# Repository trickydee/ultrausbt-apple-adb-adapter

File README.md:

# Apple ADB USB & Bluetooth Adapter

**Firmware v2.2.3** · Product: **ultrausbt-Apple-ADB-adapter** · License: [GPL-3.0-or-later](./LICENSE) · [COPYING](./COPYING) · [Release notes](./docs/release-notes.md)

## Overview

This project uses a Raspberry Pi Pico to connect modern USB and Bluetooth devices such as keyboards, mice, trackballs, and gamepads to classic Apple Desktop Bus (ADB) computers.

It targets **68K Macintosh** (Classic / LC / Quadra-class), **early PowerPC** ADB Macs (Performa / Power Macintosh), and the **Apple IIgs**.
It should also work with ADB-enabled **NeXT** machines, but these have **not** been tested yet.

A design for a reference adapter is included in the repo. The adapter is bi-directional and can be toggled between device or host mode:

* **ADB Device** mode (default): attach USB and Bluetooth devices to an ADB host computer.

* **ADB Host** mode: connect original ADB devices (keyboard, mouse, trackballs, …) to a USB HID host such as a modern PC or Mac

The hardware can be configured with dual Mini-DIN ADB ports, wired as a bus **pass-through**: you can daisy-chain real ADB keyboards, mice, trackballs, and other devices alongside the adapter’s USB/BT emulation (see [`docs/adb-passthrough-hub.md`](./docs/adb-passthrough-hub.md)).

If you are using a **Pico 2 W** you can mix USB and Bluetooth devices. USB-only builds work on Pico / Pico 2 as well. A **Pico 2 W** is recommended for the full feature set (Bluetooth + Device/Host toggle).

**This project and firmware descend from the HIDHopper ADB project and its upstream line (including QuokkADB / adbuino)** (GPL) — see Acknowledgements below.

## USB device support

* USB HID keyboards
* USB HID mice (and many trackballs that appear as mice)
* Bluetooth keyboards, mice, and one gamepad slot on Pico W / Pico 2 W (see Bluetooth support)

## Game controller support (Bluetooth)

One Bluetooth gamepad can be connected (Bluepad32). **Phase B** maps D-pad/buttons to keyboard keys and the left stick to mouse movement — useful without native ADB joystick firmware. Details: [`docs/gamepad-support.md`](./docs/gamepad-support.md).

Native Gravis MouseStick II (handler **0x23**) is planned for the future; see [`docs/FUTURE_WORK.md`](./docs/FUTURE_WORK.md).

# Usage

## USB

Connect devices to the Pico USB port (use a powered USB OTG hub if you need several). Supported keyboards and mice should enumerate within a few seconds; confirm on the OLED.

**Before powering on the Mac:** plug the adapter into ADB (and any pass-through ADB devices into the second port), attach USB/BT peripherals, then power on the host. **You should not hot-plug** ADB devices while the vintage machine is running.

## Bluetooth support (Pico W / Pico 2 W)

Bluetooth keyboards, mice, and gamepads are supported via [Bluepad32](https://github.com/ricardoquesada/bluepad32). You can run a mostly wireless ADB setup, or mix USB and Bluetooth. Prefer **Pico 2 W** for Bluetooth builds.

### Pairing

1. Put the Bluetooth device into pairing mode.
2. Confirm it on the OLED **Devices** / **Map Devices** screens.
3. Recommended order when pairing several devices (especially on Mac cold boot): **mouse → keyboard → gamepad**.

To clear stored pairing keys, hold **˄ + ˯** (Up + Down) for about five seconds (Map Devices shows `^+~ Clear Pair`).

More detail: [`docs/bluetooth-pairing.md`](./docs/bluetooth-pairing.md).

## ADB Device mode (USB/BT → vintage ADB host)

Default mode. Attach USB and Bluetooth keyboards, mice, trackballs, and (on Pico W / Pico 2 W) a gamepad to an ADB host:

* Apple IIgs
* Macintosh 68K (Classic / LC / Quadra-class)
* Early PowerPC ADB Macs

**NeXT** machines have **not** been tested yet.

Pass-through port: real ADB devices can share the bus with the adapter.

## ADB Host mode (ADB devices → modern USB host)

Connect ADB devices (keyboard, mouse, trackball, …) to a USB host such as a modern PC or Mac. The adapter polls the ADB bus and presents them as USB HID.

* Switch with **`*`** from any OLED screen, or use the **ADB Mode** page (`#` carousel → Mode; `˄`/`˯` select **ADB Host** / **ADB Device**, `#` apply). Homescreen shows **ADB Host** or **ADB Dev**.
* Vintage Mac / IIgs should be **off and disconnected**; remove USB-A peripherals while in ADB Host mode (Bluetooth is not bridged to the PC in this mode).
* Details: [`docs/adb-host-mode.md`](./docs/adb-host-mode.md).

# OLED UI

An SSD1306 OLED and four buttons are supported on the UltraUSBT ADB board — the display is optional on a bare Pico, but recommended:

| Key | Role |
|-------|------|
| **˄** (Up) | Mode screen: select **ADB Host**; with ˯: clear BT pairings |
| **˯** (Down) | Mode screen: select **ADB Device**; with ˄: clear BT pairings |
| **#** (Center) | Advance screen carousel; Mode screen: apply |
| **\*** | Toggle ADB Device ↔ ADB Host from any screen |

Carousel (host builds): Splash → Devices → Map Devices → ADB Bus → ADB Mode → Splash.

# Hardware

The [`kicad/`](./kicad/) directory holds the **reference board** design for this project (KiCad schematic / PCB — dual Mini-DIN ADB pass-through, BSS138 level shifting, Pico).

Firmware GPIO and power notes: [`docs/hardware.md`](./docs/hardware.md).

# Building the firmware

Download a pre-built UF2 from [Releases](https://github.com/trickydee/ultrausbt-apple-adb-adapter/releases), or build with `./build-all.sh`:

```bash
# Default: Pico 2 W (device + host toggle) → dist/
./build-all.sh

# Quick single-board dev build
./build.sh
```

Flash the matching `.uf2` from `dist/` (hold **BOOTSEL**, copy to the RPI-RP2 drive).

Typical outputs:

* `dist/ultrausbt-Apple-ADB-adapter-firmware-pico2_w-host.uf2` — release image (**ADB Device** and **ADB Host**)
* `dist/ultrausbt-Apple-ADB-adapter-firmware-pico2_w-host-debug.uf2` — UART debug @ 115200 on GP0

If `PICO_SDK_PATH` is unset, the scripts clone the Pico SDK once under `.pico-sdk/`. Optional upstream TinyUSB: `git submodule update --init --recursive`.

# Documentation

| Doc | Topic |
|-----|--------|
| [`docs/release-notes.md`](./docs/release-notes.md) | Firmware changelog |
| [`docs/troubleshooting.md`](./docs/troubleshooting.md) | Common issues, BT pairing, host timing |
| [`docs/bluetooth-pairing.md`](./docs/bluetooth-pairing.md) | Multi-device Bluetooth tips |
| [`docs/adb-host-mode.md`](./docs/adb-host-mode.md) | ADB Host mode (ADB devices → modern USB host) |
| [`docs/adb-passthrough-hub.md`](./docs/adb-passthrough-hub.md) | Pass-through / hub behaviour |
| [`docs/gamepad-support.md`](./docs/gamepad-support.md) | BT gamepad mapping |
| [`docs/iigs-debugging.md`](./docs/iigs-debugging.md) | IIgs timing notes |
| [`docs/hardware.md`](./docs/hardware.md) | Board / GPIO |
| [`docs/build-flags.md`](./docs/build-flags.md) | CMake options |
| [`docs/FUTURE_WORK.md`](./docs/FUTURE_WORK.md) | Roadmap |
| [`docs/changes.md`](./docs/changes.md) | Version / SDK build notes |
| [`docs/archive/`](./docs/archive/) | Historical port / design notes |
| [`docs/fixtures/`](./docs/fixtures/) | ADB captures (adbmon, Wacom, SE/30) |

## Contributions

This project is open source — pull requests and issues are welcome. See [`CONTRIBUTING.md`](./CONTRIBUTING.md).

# Acknowledgements

This project was made possible by the "HID Hopper" project from Androda which in turn benefited from other upstream projects.

**Upstream — please support the original projects with a GitHub star:**

* **HIDHopper ADB** [HIDHopper_ADB](https://github.com/TechByAndroda/HIDHopper_ADB) — the ADB-on-Pico lineage this firmware continues
* **adbuino** [akuker/adbuino](https://github.com/akuker/adbuino)
* **QuokkADB** [QuokkADB-firmware](https://github.com/rabbitholecomputing/QuokkADB-firmware)
* **tmk_keyboard** [tmk_keyboard](https://github.com/tmk/tmk_keyboard) — ADB protocol foundations
* **bbraun** [bbraun’s adbduino](http://synack.net/svn/adbduino/)
* **Difegue** [Difegue’s updates](https://tvc-16.science/adbuino-ps2.html) — early adbuino / PS/2 work

This fork also relies on:

* [Raspberry Pi Pico SDK](https://github.com/raspberrypi/pico-sdk) — RP2040 / RP2350 platform
* [TinyUSB](https://github.com/hathach/tinyusb) by Ha Thach — USB host and device stacks
* [Bluepad32](https://github.com/ricardoquesada/bluepad32) by Ricardo Quesada — Bluetooth HID

**Other UltraUSBT projects**

If this project is useful you may also want to check out:

* Amiga Keyboard and Dual DSub 9 pin adapter — [Amiga USB/BT adapter](https://github.com/trickydee/ultrausbt-amiga)

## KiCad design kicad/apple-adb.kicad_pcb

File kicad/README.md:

# UltraUSBT reference hardware

KiCad schematic and PCB files for the UltraUSBT DIY Apple ADB adapter live in this directory.

Firmware GPIO and wiring notes: [`../docs/hardware.md`](../docs/hardware.md).

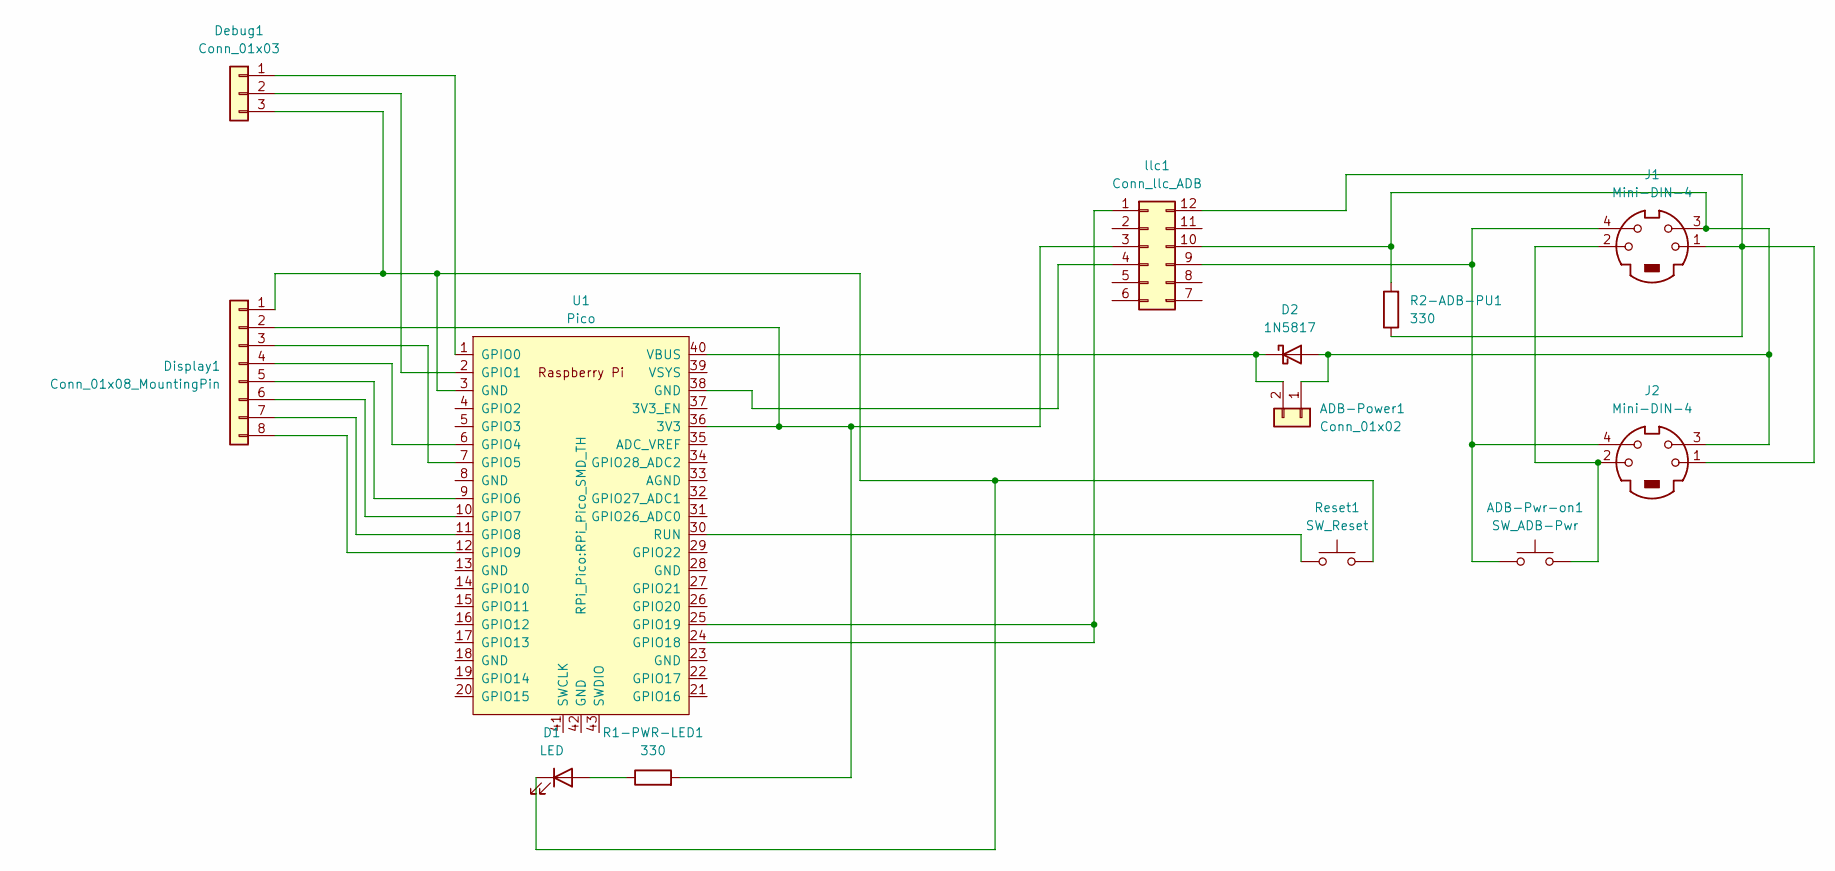
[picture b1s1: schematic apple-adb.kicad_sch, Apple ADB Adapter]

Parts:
ADB-Power1: Conn_01x02; PinSocket_1x02_P2.54mm_Vertical
ADB-Pwr-on1: SW_ADB-Pwr; SW_PUSH_6mm
D1: LED; LED_D3.0mm
D2: 1N5817; D_DO-41_SOD81_P10.16mm_Horizontal
Debug1: Conn_01x03; PinSocket_1x03_P2.54mm_Vertical
Display1: Conn_01x08_MountingPin; PinSocket_1x08_P2.54mm_Vertical
J1, J2: Mini-DIN-4; ADB_MDR4_MINI-DIN
R1-PWR-LED1, R2-ADB-PU1: 330; R_Axial_DIN0204_L3.6mm_D1.6mm_P7.62mm_Horizontal
Reset1: SW_Reset; SW_PUSH_6mm
U1: Pico; RPi_Pico_SMD_TH
llc1: Conn_llc_ADB; DIP-12_W10.16mm

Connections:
unnamed: ADB-Power1.1, D2.2 (A), J1.3, J2.3, R2-ADB-PU1.2, llc1.10 (Pin_b3)
unnamed: ADB-Power1.2, D2.1 (K), U1.40 (VBUS)
unnamed: ADB-Pwr-on1.2, J1.2, J2.2
unnamed 3: D1.2 (A), R1-PWR-LED1.1; also elsewhere on the board
unnamed 4: D1.1 (K), Debug1.3, Display1.1, Reset1.2, U1.3 (GND); also elsewhere on the board
unnamed: Debug1.1, U1.1 (GPIO0)
unnamed: Debug1.2, U1.2 (GPIO1)
unnamed: Display1.2, R1-PWR-LED1.2, U1.36 (3V3), llc1.3 (Pin_a3)
unnamed: Display1.3, U1.7 (GPIO5)
unnamed: Display1.4, U1.6 (GPIO4)
unnamed: Display1.5, U1.9 (GPIO6)
unnamed: Display1.6, U1.10 (GPIO7)
unnamed: Display1.7, U1.11 (GPIO8)
unnamed: Display1.8, U1.12 (GPIO9)
unnamed: U1.24 (GPIO18), U1.25 (GPIO19), llc1.1 (Pin_a1)
unnamed: Reset1.1, U1.30 (RUN)
unnamed: U1.38 (GND), llc1.4 (Pin_a4)
unnamed: J1.1, J2.1, R2-ADB-PU1.1, llc1.12 (Pin_b1)
unnamed: ADB-Pwr-on1.1, J1.4, J2.4, llc1.9 (Pin_b4)

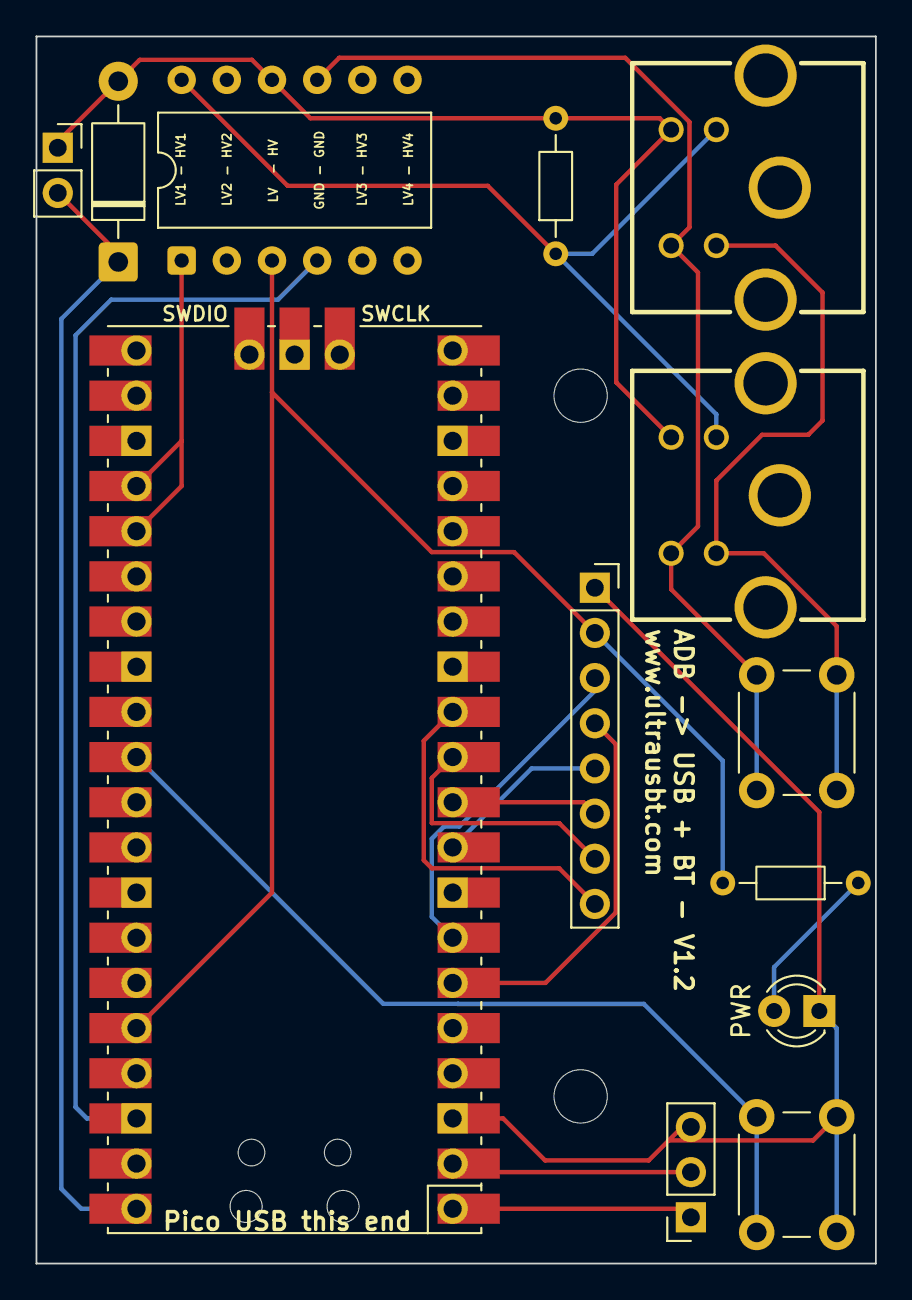
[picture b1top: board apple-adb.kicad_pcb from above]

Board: 2 copper layers, 47.2 x 69.0 mm, 13 parts (0 on the bottom side), 19 nets.

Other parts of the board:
PWR: LED; LED_D3.0mm

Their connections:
unnamed 3: PWR.2 (A); also elsewhere on the board
unnamed 4: PWR.1 (K); also elsewhere on the board

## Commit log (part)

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2026-03-05 Add build setup, update ADB GPIOs, add docs/changes
    - Add top-level Makefile and build.sh for firmware build
    - Update README with build-from-root instructions
    - ADB GPIOs: ADB_OUT_GPIO=18, ADB_IN_GPIO=19 (was 19/20)
    - Fix set_sys_clock_khz: add hardware/clocks.h and hardware_clocks link
    - Add docs/changes.md documenting GPIO configuration
2026-03-05 Add upstream TinyUSB, Blue-QuokkADB name, SDK 2.2.0
    - Add TinyUSB as submodule at src/firmware/tinyusb (optional upstream)
    - Set PICO_TINYUSB_PATH in CMake when tinyusb/hw/bsp/rp2040 present
    - build.sh: init submodules; README and docs/changes: document upstream TinyUSB
    - pico_sdk_import: default fetch tag 2.2.0, GIT_SUBMODULES_RECURSE TRUE
    - Product name: Blue-QuokkADB (platform_config.h)
    - Add <cstdio> in platformkbdparser.cpp and quokkadb.cpp for printf
2026-03-05 Add Bluepad32 (BT keyboard/mouse) and build_all.sh
    - Add bluepad32 submodule, init/platform (keyboard+mouse only), bt_hid_bridge
    - Enable Bluepad32 for pico_w and pico2_w in CMake; feed BT into same ADB parsers as USB
    - Add build_all.sh: build-pico, build-pico_w, build-pico2, build-pico2_w
    - Ignore build-* directories in .gitignore; update docs/changes.md
2026-03-06 Add firmware version (1.0.1), fix flash sector conflict with BTstack
    - Single source of truth: project VERSION in firmware CMakeLists.txt
    - platform_config.h uses HIDHopper ADB version for banner/identity
    - docs/changes.md: document version and how to bump
    - flashsettings: move settings off last sector to avoid BTstack TLV overlap
2026-03-06 CMakeLists.txt: minor whitespace/formatting
2026-03-06 v1.0.2: fix right-mouse hang, add release notes
    - Remove blocking waits in ctrl-click path (usbmouseparser.cpp) so device
    no longer hangs on right mouse button; ctrl-click still works for System 6/7
    - Bump firmware version to 1.0.2
    - Add docs/release-notes.md with 1.0.2 and 1.0.1 entries
2026-03-06 docs: add 1.0.0 release notes (supported boards, Bluepad32)
2026-03-06 Initial screen commit: SSD1306 OLED display (Apple ADB)
    - Add ssd1306 driver and font (from amigahid-pico, MIT)
    - Display module: splash (Apple ADB, version, mode), devices, BT names
    - I2C on GPIO 4/5 (i2c0), buttons 6/7/8; no GPIO collision with ADB/LED/UART
    - Integrate display_init, display_show_splash, display_handle_buttons in main loop
    - BT device counts and display_set_bt_counts when Bluepad32 enabled
    - docs/changes.md: document display GPIOs and config
2026-03-06 Display ADB status (K/M/G, SRQ, collision), fix disconnect detection, build script
    - Splash ADB line: show device IDs (K# M# G#), S for SRQ, ! for collision
    - Only redraw splash on connection/ID change (not SRQ/collision) to avoid
    mouse lag from full-screen I2C refresh
    - Show 'ADB: --' when unplugged: only refresh last_adb_cmd_time when
    ReceiveCommand returns a valid command (cmd >= 0)
    - build_all.sh: auto-set PICO_SDK_PATH from common paths or
2026-03-06 v1.0.7: Mouse wheel support, release notes for 1.0.6 and 1.0.7
    - Mouse wheel: read report->wheel, emulate as Up/Down arrow keys (USB + BT)
    - Version 1.0.7; release notes document 1.0.6 (disconnect, display refresh, build
    script) and 1.0.7 (mouse wheel)
2026-03-06 Release 1.0.10: BT platform note, pairing timing, 225MHz, docs
    - Bump version to 1.0.10
    - Release note: Bluetooth unstable on Pico W (RP2040), recommended
    Pico 2 W (RP2350) for reliable BT keyboards/mice/gamepads
    - Bluetooth: 225 MHz overclock for BT builds (match Atari adapter),
    50ms post-pause delay, 200ms pre-resume, sleep_ms(1) in pause loop
    - BTstack: MAX_NR_SM_LOOKUP_ENTRIES 4, config comments aligned with
2026-03-07 saving context
2026-03-11 IIGS ADB: wider timing, targeted RX failure logging
    - Attention window: accept 500-950µs (IIGS ~500-650µs)
    - Sync/start bit: 25-105µs (was 30-95µs)
    - Bit cell: allow up to 145µs total (was 130µs)
    - Log receive failures as ADB RX fail: ATTENTION/SYNC/BIT with timing
    when global_debug, for diagnostics without flooding
2026-03-12 IIGS: spec-aligned receive timing + debugging doc
    - Receive16bitRegister: Tlt 140-260µs (was 130-270); bit cell 70-130µs
    - ReceiveCommand: bit cell 70-130µs (was up to 145µs)
    - docs/iigs-debugging.md: parameter tweaks and scope notes for further debug
2026-03-24 docs: add ADB Apple IIgs receive timing summary
    Summarize attention, sync, bit-cell, and Tlt differences vs feature/display,
    with file references and pointer to iigs-debugging.md.
2026-03-24 docs: add ADB Apple IIgs receive timing summary (from IIGS-Fixes)
    Same content as docs/adb-iigs-support.md on feature/IIGS-Fixes.
2026-03-25 docs: add Apple IIgs Hardware Reference ADB timing summary
    Table 6-8 bounds, duty-cycle rules, SRQ/global reset notes, and
    comparison with Guide to Macintosh Family Hardware; link from adb-iigs-support.
2026-03-25 docs: sync adb-iigs-support.md from feature/display
    Include adb-iigs-hardware-reference.md so the new cross-link resolves.
2026-03-25 IIGS ADB: align attention + reset timing to IIgs ref
    - ReceiveCommand attention window: 560–1040 µs (IIgs HW Ref Table 6-8)
    - Global reset detect threshold: >= 2.8 ms
    - Update SRQ comment to match IIgs timings
2026-03-25 docs+fw: bump version and label IIgs build
    - Bump firmware version to 1.0.8
    - Splash title shows IIGS for IIgs-timing work
    - Add alignment plan doc
2026-03-25 IIGS ADB: duty-cycle decode bits per hardware reference
    Decode bits by low-time fraction of measured bit-cell:
    - low < 35% => 1
    - low > 65% => 0
    - otherwise reject frame
    Applies to ReceiveCommand and Receive16bitRegister.
2026-03-25 IIGS ADB: fix phase-b decode regression
    Use measured-cell midpoint duty decode (<50% => 1, >=50% => 0)
    instead of rejecting 40-60% duty values that caused command loss.
2026-03-25 IIgs ADB: attention slack, LISTEN16 decode, keyboard NO_KEY handling
    Lower the attention low floor to 500 µs so measured ~560 µs IIgs pulses
    are accepted on RP2040, and log 400–499 µs near-misses for tuning.
    Relax Receive16bitRegister start-bit and bit-cell checks so mouse LISTEN
    reg 3 fails less often under IIgs timing.
    When USB maps to 0xFF (unmapped / NO_KEY), do not set key-up; pack the
    second key with separate locals to avoid corrupt register merging.
2026-03-25 Firmware 1.0.9: lower ADB attention floor to 450 µs
    IIgs attention often measures high-400s µs on RP2040; accept >=450 to
    reduce dropped polls. Adjust debug near-miss logging to 380–449 µs.
2026-03-26 Release 1.0.10 with configurable IIgs mouse/attention tuning.
    Add build-time toggles for accumulated mouse deltas and attention low-floor A/B testing, update docs and release notes, and include a Pico 2 W-focused A/B build script to simplify real-hardware valid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
2026-03-26 docs: record IIgs and Quadra validation results
    Document the latest cross-host testing results in the IIgs support notes and 1.0.10 release notes to capture that the same tuned firmware improved behavior on both Apple IIgs and Mac Quadra.
2026-03-26 IIgs default: suppress mouse SRQ to avoid BASIC slowdown
    Enable `ADB_IIGS_MOUSE_SUPPRESS_SRQ=ON` for builds produced by `build_all.sh`, and document the new behavior along with the Phase C/B/A toggles and test scripts.
2026-04-03 Fork cleanup, IIgs defaults, docs, and build helper
    - Remove unused ADBuino/PlatformIO paths; simplify main and USB/ADB includes
    - Default ADB_IIGS_MOUSE_SUPPRESS_SRQ=ON in CMake; document disable flag
    - Splash OLED: Apple ADB / ultramegausb.com; firmware v1.0.15
    - LICENSE/README: fork lineage; TinyUSB + Bluepad32; ignore build-*/ and dist/
    - Docs: consolidate under docs/ (HIDHopper, adb, wacom), build-flags, led-support, todo
    - Remove case/, cc-nc-hw/, extra images; build_all.sh uses scripts/lib/build_common.sh
2026-04-03 Rename project to BT-USB-ADB-Adapter (firmware 1.0.16)
    - CMake target BT-USB-ADB-Adapter-firmware; UF2 and dist names updated
    - PRODUCT_NAME, version macro BT_USB_ADB_ADAPTER_VERSION_STRING, BLE name
    - README and LICENSE describe new name; HIDHopper provenance kept in docs
    - Release notes 1.0.16; changes/build-flags/adb-iigs-support paths aligned
2026-04-03 Build: shared .pico-sdk cache, picotool path, cleanup option (v1.0.17)
    - Clone Pico SDK once to .pico-sdk/pico-sdk; set PICOTOOL_FETCH_FROM_GIT_PATH
    - scripts/cmake_with_pico_sdk.sh for Makefile; build.sh sources build_common
    - cleanup: --include-sdk-cache removes .pico-sdk; default clean keeps cache
    - Document in README and docs/changes.md; release notes 1.0.17
2026-04-03 Gamepad: flash layout vs BTstack, BT/USB cooperation, docs
    Place FlashSettings one sector below the SDK BTstack TLV bank so settings
    erase/program never overlaps link-key storage (notably RP2350 A2 layout).
    Add bt_host_coop and extend bluepad32_platform, bt_hid_bridge, and display
    for stable Bluetooth gamepad use on Pico 2 W. Document flash layout and
    gamepad behavior in docs/gamepad-support.md; touch README and release notes.
2026-06-24 Align OLED UI with ultramegausb spec and document BT pairing work.
    Splash/Devices/Map Devices screens, USB device map for Map Devices, L+R pairing clear, and pairing handoff docs for a future stability port.
2026-06-24 Improve ADB hub enumeration, BT HID merging, and gamepad mouse feel.
    Use host-driven address assignment in hub mode instead of hard-coded
    addresses; fix idle button polling when no ADB host is present. Merge up to
    two BT mice, latch BT button state during movement-only BLE reports, and
    apply gamepad stick deltas with replace semantics. Document GP_MOUSE tuning
    and future multi-cursor support.
2026-06-24 Fix BT mouse drag and restore reliable USB/BT movement (v1.0.18).
    Persist BLE button state in Bluepad32 and latch buttons in the HID bridge
    so drags hold without clobbering USB clicks; keep the proven ADB register-0
    snapshot path so movement and clicks stay smooth on both input paths.
2026-06-24 Gamepad click latch, hub SRQ docs, and roadmap for ADBMON/host/Gravis.
    Latch L1/R2 across gamepad mouse frames like BT mice; read USB boot wheel byte when report len allows. Document hub trackball handoff without mouse SRQ (reverted experiments); expand FUTURE_WORK for 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
2026-06-28 Add ADB host mode: multi-device bus master, USB HID bridge, and OLED status.
    Enable ADB>USB mode so vintage keyboards and pointing devices on the passthrough
    bus are polled as host, mapped to a composite USB HID device, and shown on a new
    ADB Bus screen with configured vs working detection; includes hot-plug rescan,
    trackball relocation, DIY hardware docs, and adbmon for bus capture.
2026-06-28 Bump firmware version to 2.0.0 for ADB host mode release.
    Major version reflects the new ADB>USB bus-master capability alongside existing
    USB/BT to vintage Mac device mode.
2026-06-28 Fix device mode GPIO regression; split host tri-state into adb_host_gpio.
    Restore drive-high shared ADB GPIO for ADB>Mac so collision detection works
    again (BT mouse). Keep open-collector TX in host-only code with 765 µs timing
    unchanged. Bump firmware to 2.1.0.
2026-06-28 Remove legacy QuokkADB CI, A/B build scripts, and stale dev files.
    Drop the old quokkadb_build workflow, attention/decode/mouse SRQ A/B scripts,
    QuokkADB supplementary udev/VS Code notes, and the unused firmware test README.
2026-06-30 Improve ADB host mode reliability for keyboard, trackball, and caps lock.
    Fix idle R0 handling, bus preamble timing, and device enumeration so daisy-chained
    and dual-port setups work together; sync locking caps via register 2 instead of
    forwarding 0x39; add USB LED output to ADB Listen R2; skip trackball relocation
    when a pointing device is already at 0x03.
